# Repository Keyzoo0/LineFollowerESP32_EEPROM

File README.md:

<div align="center">

# 🤖 Robot Line Follower ESP32 — EEPROM Polinema

**Line follower kompetitif berbasis ESP32 dengan _path-programming on-device_, UI OLED non-blocking, dan 7 profil PID.**
Program lintasan langsung di robot — tanpa laptop, tanpa recompile.

</div>

---

> **🔧 Status:** firmware ini telah di-**refactor total** dari arsitektur _blocking_ menjadi **non-blocking
> (cooperative state machine)** dan dimigrasikan agar **compile bersih di Arduino-ESP32 core v3.x**.
> Diverifikasi dengan `arduino-cli compile` (0 error, 0 warning).

## ✨ Sorotan Fitur

- 🧠 **Path Programming (Plan → Index → Checkpoint)** — sampai **9 plan × 100 langkah**, tiap langkah punya 14 parameter (trigger sensor, aksi, kecepatan 2-fase, PID per-segmen, timer jarak-encoder).
- 🎛️ **UI OLED non-blocking** — navigasi tab/menu responsif, tanpa _freeze_, tanpa konflik antar-menu.
- 📏 **14 sensor IR** via 2× MUX, kalibrasi **auto & manual** + pengaturan sensitivitas.
- 🎚️ **7 profil PID** yang bisa di-tune & dites _live_ di robot.
- 🏁 **Checkpoint resume** + stopwatch waktu tempuh.
- ⚫⚪ **Garis hitam & putih** didukung dalam satu lookup-table, 3 mode follow (center/kanan/kiri).
- 🔋 **Proteksi baterai** (cutoff sebelum start) + indikator persen.
- 🧰 **Tools on-device**: Test Motor, Copy/Mirror Plan, Reset Plan, Set Default, Set Throttle.

---

## 📑 Daftar Isi
1. [Quick Start](#-quick-start)
2. [Hardware](#-hardware)
3. [Arsitektur Non-Blocking](#-arsitektur-non-blocking)
4. [Peta Menu](#-peta-menu)
5. [Path Programming](#-path-programming-planindexcheckpoint)
6. [Profil PID](#-profil-pid)
7. [Apa yang Berubah di Refactor Ini](#-apa-yang-berubah-di-refactor-ini)
8. [Peta Memori](#-peta-memori)
9. [Struktur Proyek](#-struktur-proyek)
10. [Roadmap](#-roadmap)
11. [Kredit & Lisensi](#-kredit--lisensi)

---

## 🚀 Quick Start

<details open>
<summary><b>Build via arduino-cli (cara yang dipakai untuk verifikasi)</b></summary>

```bash
# 1. Pasang core ESP32 v3.x
arduino-cli config add board_manager.additional_urls https://espressif.github.io/arduino-esp32/package_esp32_index.json
arduino-cli core update-index
arduino-cli core install esp32:esp32

# 2. Pasang library
arduino-cli lib install "Adafruit GFX Library" "Adafruit SH110X" "Adafruit PCF8574" "SPIMemory"

# 3. Compile
arduino-cli compile --fqbn esp32:esp32:esp32 LineFollowerESP32_EEPROM

# 4. Upload (ganti /dev/ttyUSB0 sesuai port)
arduino-cli upload  --fqbn esp32:esp32:esp32 -p /dev/ttyUSB0 LineFollowerESP32_EEPROM
```
</details>

<details>
<summary><b>Build via Arduino IDE</b></summary>

1. **Boards Manager** → pasang `esp32 by Espressif` (versi 3.x).
2. **Library Manager** → pasang: Adafruit GFX, Adafruit SH110X, Adafruit PCF8574, SPIMemory.
3. Buka folder `LineFollowerESP32_EEPROM/`, pilih board **ESP32 Dev Module**, lalu Upload.
</details>

> ⚠️ **Setelah flash pertama**, jalankan menu **Settings → Set Default** sekali untuk menginisialisasi
> layout memori baru (`VAL_INDEX` kini 100). Lalu **Calib Sensor → Auto** untuk kalibrasi lintasan.

---

## 🔩 Hardware

| Subsistem | Komponen | Pin / Alamat |
|-----------|----------|--------------|
| **MCU** | ESP32 (240 MHz) | — |
| **Sensor garis** | 14× IR analog via 2× MUX 8-kanal (7 kiri + 7 kanan) | ADC `32` (kiri), `35` (kanan); selektor `13/14/15` |
| **Driver motor** | H-bridge (BTS7960), PWM LEDC 15 kHz / 8-bit | Kiri `26/27` · Kanan `17/16` |
| **Encoder** | 2× rotary quadrature (CPR 208, roda Ø17 mm) | Kiri `33/25` · Kanan `39/36` |
| **Display** | OLED SH1106 128×64 I²C | `0x3C` |
| **Tombol** | 6 tombol via PCF8574 (I²C expander) | `0x27` |
| **Memori lintasan** | SPI Flash Winbond 4MB (SPIMemory) | CS `5` |
| **Memori konfigurasi** | EEPROM emulasi 1 KB | — |
| **Baterai** | ADC + divider 10k/3.3k, filter EMA, cutoff 11.8 V | `34` |
| **LED status** | indikator tulis memori | `12` |

> PCB (KiCad) & model 3D tersedia di folder [`Electrical/`](Electrical) dan [`3d Model/`](3d%20Model).

---

## 🧩 Arsitektur Non-Blocking

Versi lama menjebak eksekusi di `while(1)` tiap menu (blocking) + tombol _busy-wait_ + state global dipakai
bersama → tidak responsif & sering konflik antar-menu. Versi ini memakai **loop kooperatif**:

```mermaid
flowchart LR
    L([loop]) --> I[inputUpdate<br/>baca 6 tombol sekali<br/>edge + auto-repeat]
    I --> H[uiHandle<br/>logika layar aktif]
    H --> F{sudah 33 ms?}
    F -- ya --> R[uiRender<br/>1x lcd.display per frame]
    F -- tidak --> L
    R --> L
```

**3 pilar yang menghilangkan blocking & konflik:**

| Pilar | Sebelum | Sesudah |
|-------|---------|---------|
| **Input** | `touchUp()` _busy-wait_ menunggu tombol dilepas | `inputUpdate()` non-blocking → event `PRESS / HOLD / RELEASE` (debounce + auto-repeat berbasis `millis()`) |
| **Render** | `clearDisplay()/display()` berserak di tiap layar | satu `lcd.display()` per frame (~30 fps) |
| **State** | global `selectSet/countMenu/halIdx` dipakai bersama | tiap layar punya **struct state lokal** + **screen stack** (push/pop) |

Navigasi antar-layar memakai state machine + stack:

```mermaid
stateDiagram-v2
    [*] --> HOME
    HOME --> MENU: OK
    HOME --> SETINDEX: Set Plan
    HOME --> CHECKPOINT
    HOME --> CALIB
    HOME --> RACE: RUN (mode C)
    HOME --> TUNEPID: RUN (mode F)
    MENU --> SETTINGS
    MENU --> TUNEPID
    MENU --> TESTMOTOR
    MENU --> COPYMIRROR
    MENU --> RESETPLAN
    SETINDEX --> ADDREMOVE
    SETTINGS --> SETDEFAULT
    SETTINGS --> THROTTLE
    RACE --> RACE_RESULT
    RACE_RESULT --> HOME
```

> 🏁 **Mode balapan** sengaja tetap _tight loop_ real-time (deterministik untuk kontrol), namun tombol
> abort dibaca non-blocking dan **semua timing pakai `millis()`** (tanpa `delay()`), jadi abort tetap responsif.

---

## 🗺️ Peta Menu

<details open>
<summary><b>Pohon menu lengkap</b></summary>

```
HOME ── UP/DOWN pindah widget · RUN = mulai ──────────────────────────
├─ Mode C/F        C=Balapan, F=Tune PID   ·  OK → MAIN MENU
├─ Set Plan        pilih plan (1–9)         ·  OK → SET INDEX
├─ Normal Speed    ±5
├─ CHKPNT          OK → CHECKPOINT
└─ CALSEN          OK → CALIB SENSOR

MAIN MENU ── UP/DOWN · RUN = back ────────────────────────────────────
├─ Set Plan          OK → SET INDEX
├─ Calib Sensor      +:Auto   -:Manual
├─ Tuning PID        OK → TUNE PID
├─ Test Motor        OK → TEST MOTOR
├─ Copy Mirror Plan  OK → COPY/MIRROR
├─ Delete Plan       OK → RESET PLAN
└─ Settings          OK → SETTINGS (Set Default · Set Throttle)

SET INDEX ── editor langkah (list datar, 15 baris) ───────────────────
   Index · Trig SLog · Trig Logic · Action · Speed L/R · Act Delay ·
   PID Prof · Speed A · Timer A · Mode TIM · Speed B · Timer B ·
   UsedSens · FL Mode      (OK di baris "Index" → ADD/REMOVE langkah)
```
</details>

**Tombol:** `OK` pilih/masuk · `UP/DOWN` navigasi · `+ / -` ubah nilai (tahan = auto-repeat) · `RUN` kembali/mulai.

---

## 🧠 Path Programming (Plan/Index/Checkpoint)

Robot menjalankan **program lintasan** yang tersimpan, bukan sekadar mengikuti garis.

- **Plan** = satu lintasan penuh (ada **9** plan).
- **Index** = satu langkah dalam plan (ada **100** langkah/plan). Tiap langkah menyimpan:

| Parameter | Fungsi |
|-----------|--------|
| `Trig SLog` + `Trig Logic` | **Pemicu**: pola sensor + logika `OR / AND / TIM / XOR` |
| `Action` | aksi saat terpicu: `STOP/FORWARD/LEFT/RIGHT/BACKWARD/PICK/DROP/TLEFT/TRIGHT/FAN` |
| `Speed L/R` + `Act Delay` | kecepatan & durasi aksi |
| `Speed A/B` + `Timer A/B` | **2 fase kecepatan** dengan ramp berbeda |
| `Mode TIM` | sumber timer: waktu `mS` atau **jarak encoder** `CmR/CmL` |
| `PID Prof` | profil PID per-segmen (Normal..Profil 6) |
| `UsedSens` | masking sensor pinggir (All / Ignore 1–3 sisi) |
| `FL Mode` | sisi garis: `FLC` center · `FLR` kanan · `FLL` kiri |

- **Checkpoint** = titik _resume_; robot bisa lanjut balapan dari langkah tertentu (8 CP/plan).

```mermaid
flowchart TD
    S[start] --> RD[baca sensor]
    RD --> TR{pemicu langkah<br/>terpenuhi?}
    TR -- tidak --> PID[ikuti garis PID<br/>normalSpeed] --> RD
    TR -- ya --> ACT[eksekusi Action] --> A[fase A: ramp ke Speed A<br/>selama Timer A]
    A --> B[fase B: ramp ke Speed B<br/>selama Timer B]
    B --> ST{langkah == stop?}
    ST -- tidak --> NX[langkah++] --> RD
    ST -- ya --> F([selesai: tampil waktu])
```

---

## 🎚️ Profil PID

7 profil tersimpan di EEPROM, di-tune lewat **Tuning PID** (+ uji _live_ "Coba PID"):

| Profil | Kp | Ki | Kd | Target v |
|:------:|:--:|:--:|:--:|:--------:|
| Normal | 3.0 | 0.00 | 10 | 50 |
| Profil 1 | 7.0 | 0.02 | 12 | 80 |
| Profil 2 | 7.0 | 0.02 | 15 | 100 |
| Profil 3 | 7.4 | 0.04 | 35 | 120 |
| Profil 4 | 7.4 | 0.04 | 40 | 140 |
| Profil 5 | 7.4 | 0.04 | 50 | 160 |
| Profil 6 | 7.4 | 0.04 | 60 | 180 |

Hukum kontrol: `move = error·Kp + ΣError·Ki + Δerror·Kd` → `kiri = v − move`, `kanan = v + move` (clamp ±255).

---

## 🔄 Apa yang Berubah di Refactor Ini

<details>
<summary><b>🐞 Bug yang diperbaiki</b></summary>

| # | Bug | Perbaikan |
|---|-----|-----------|
| 1 | `VAL_INDEX=50` tapi UI memakai index 0–99 → **buffer overflow** | dinaikkan ke **100** + serialisasi flash diperbarui |
| 2 | Hanya 5 dari 9 plan dibaca saat boot (`readIdx` loop `<5`) | dimuat penuh `< VAL_PLAN` |
| 3 | `analogReadResolution(8)` vs kalibrasi skala 1023 | disamakan ke **10-bit** (battery ikut diperbaiki ÷1023) |
| 4 | `accelTA/accelTB` diatur tapi tak dipakai | kini **benar-benar dipakai** sebagai step ramp fase A/B |
| 5 | Transfer Plan tak terjangkau / stub | dihapus dari menu (out-of-scope) |
| 6 | `guiTestMotor` `speedsR == 255` (operator salah) | ditulis ulang dengan clamp benar |
| 7 | Duplikasi `struct Plan/CP` global (~15 KB) + bug sinkronisasi | dihapus, serialisasi via blob transien |

</details>

<details>
<summary><b>⚙️ Migrasi Arduino-ESP32 v3.x (LEDC)</b></summary>

| Lama (v2.x) | Baru (v3.x) |
|-------------|-------------|
| `ledcSetup(ch, freq, res)` + `ledcAttachPin(pin, ch)` | `ledcAttach(pin, freq, res)` |
| `ledcWrite(ch, duty)` | `ledcWrite(pin, duty)` |

Terisolasi di `motor.ino` — logika kontrol tidak berubah.
</details>

---

## 💾 Peta Memori

**EEPROM (1 KB)** — konfigurasi: home (0–3), sensitivity (4), max/min sensor (6–61), kalibrasi (62–89),
Kp/Ki/Kd (90–110), accel (111–112).

**SPI Flash 4MB** — lintasan: 9 plan × 1700 B + 9 checkpoint × 32 B ≈ **15.6 KB** (muat dalam `eraseBlock32K`).
Serialisasi memakai **blob transien** — tidak ada duplikasi RAM.

---

## 📂 Struktur Proyek

| Lapisan | File | Peran |
|---------|------|-------|
| **Entry** | `LineFollowerESP32_EEPROM.ino` | `setup()` + `loop()` (input → handle → render) |
| **Data** | `data.h`, `storage.ino` | konfigurasi, plan, checkpoint, save/load |
| **Input** | `input.h`, `input.ino` | tombol non-blocking (PCF8574) |
| **UI** | `ui.h`, `ui.ino` | state machine + dispatcher |
| **Layar** | `screens_main.ino`, `screens_index.ino`, `screens_tools.ino` | semua menu |
| **Kontrol** | `PID.ino`, `sensor.ino`, `motor.ino`, `encoder.ino`, `race.ino` | follow line + balapan |
| **Display** | `oled.h`, `oled.ino` | SH1106 + bitmap + helper gambar |
| **Util** | `timer.h` | stopwatch millis |

---

## 🛣️ Roadmap

Fitur berikut sengaja **di-tunda** (hardware belum ada / out-of-scope) agar fokus pada line follower:

- [ ] Transfer Plan (robot ↔ robot)
- [ ] Gripper & Fan (aksi `PICK/DROP/FAN` kini no-op)
- [ ] Setting Encoder (PID kecepatan)
- [ ] Wi-Fi + OTA Update
- [ ] Mode Transporter

---

## 🙏 Kredit & Lisensi

Dirancang oleh **Komunitas EEPROM Polinema** (tim G14/G15).
Refactor arsitektur non-blocking & migrasi core v3.x.

Lisensi **MIT** © 2024 [Keyzoo0](https://github.com/Keyzoo0) — lihat [LICENSE](LICENSE).

<div align="center">

⭐ _Kalau proyek ini membantu, kasih bintang ya!_ ⭐

</div>

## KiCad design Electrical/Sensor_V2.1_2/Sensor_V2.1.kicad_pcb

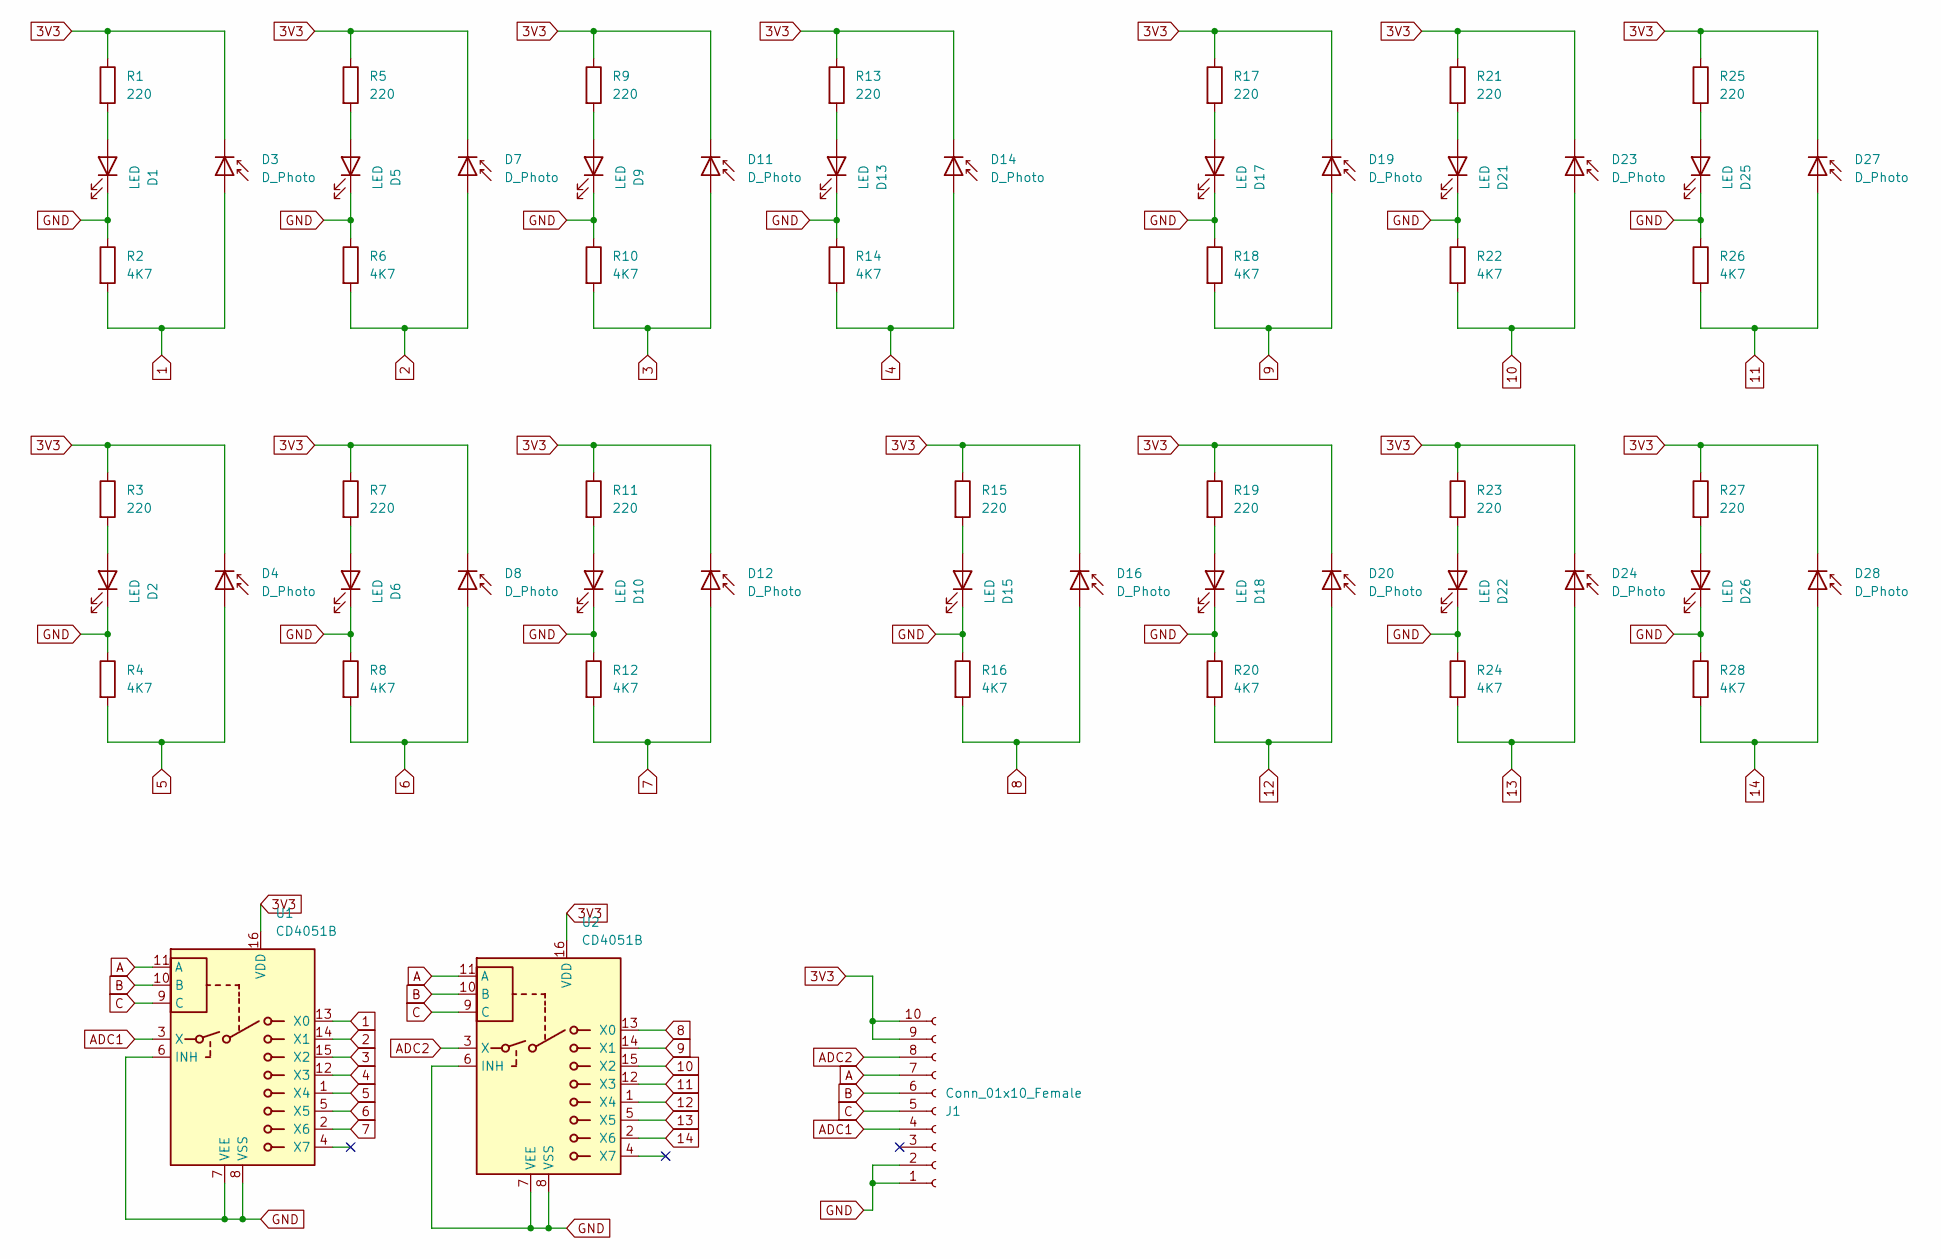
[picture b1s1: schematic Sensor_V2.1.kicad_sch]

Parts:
D1, D2, D5, D6, D9, D10, D13, D15, D17, D18, D21, D22, D25, D26: LED; LED_D3.0mm
D3, D4, D7, D8, D11, D12, D14, D16, D19, D20, D23, D24, D27, D28: D_Photo; LED_D3.0mm
J1: Conn_01x10_Female; TE_1-84952-0_1x10-1MP_P1.0mm_Horizontal
R1, R3, R5, R7, R9, R11, R13, R15, R17, R19, R21, R23, R25, R27: 220; R_0805_2012Metric_Pad1.20x1.40mm_HandSolder
R2, R4, R6, R8, R10, R12, R14, R16, R18, R20, R22, R24, R26, R28: 4K7; R_0805_2012Metric_Pad1.20x1.40mm_HandSolder
U1, U2: CD4051B; SOIC-16_3.9x9.9mm_P1.27mm

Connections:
1: D3.2 (A), R2.2, U1.13 (X0)
2: D7.2 (A), R6.2, U1.14 (X1)
3: D11.2 (A), R10.2, U1.15 (X2)
3V3: D3.1 (K), D4.1 (K), D7.1 (K), D8.1 (K), D11.1 (K), D12.1 (K), D14.1 (K), D16.1 (K), D19.1 (K), D20.1 (K), D23.1 (K), D24.1 (K), D27.1 (K), D28.1 (K), J1.9, J1.10, R1.1, R3.1, R5.1, R7.1, R9.1, R11.1, R13.1, R15.1, R17.1, R19.1, R21.1, R23.1, R25.1, R27.1, U1.16 (VDD), U2.16 (VDD)
4: D14.2 (A), R14.2, U1.12 (X3)
5: D4.2 (A), R4.2, U1.1 (X4)
6: D8.2 (A), R8.2, U1.5 (X5)
7: D12.2 (A), R12.2, U1.2 (X6)
8: D16.2 (A), R16.2, U2.13 (X0)
9: D19.2 (A), R18.2, U2.14 (X1)
10: D23.2 (A), R22.2, U2.15 (X2)
11: D27.2 (A), R26.2, U2.12 (X3)
12: D20.2 (A), R20.2, U2.1 (X4)
13: D24.2 (A), R24.2, U2.5 (X5)
14: D28.2 (A), R28.2, U2.2 (X6)
A: J1.7, U1.11 (A), U2.11 (A)
ADC1: J1.4, U1.3 (X)
ADC2: J1.8, U2.3 (X)
B: J1.6, U1.10 (B), U2.10 (B)
C: J1.5, U1.9 (C), U2.9 (C)
GND: D1.1 (K), D2.1 (K), D5.1 (K), D6.1 (K), D9.1 (K), D10.1 (K), D13.1 (K), D15.1 (K), D17.1 (K), D18.1 (K), D21.1 (K), D22.1 (K), D25.1 (K), D26.1 (K), J1.1, J1.2, R2.1, R4.1, R6.1, R8.1, R10.1, R12.1, R14.1, R16.1, R18.1, R20.1, R22.1, R24.1, R26.1, R28.1, U1.6 (INH), U1.7 (VEE), U1.8 (VSS), U2.6 (INH), U2.7 (VEE), U2.8 (VSS)
unnamed: D1.2 (A), R1.2
unnamed: D2.2 (A), R3.2
unnamed: D5.2 (A), R5.2
unnamed: D6.2 (A), R7.2
unnamed: D9.2 (A), R9.2
unnamed: D10.2 (A), R11.2
unnamed: D13.2 (A), R13.2
unnamed: D15.2 (A), R15.2
unnamed: D17.2 (A), R17.2
unnamed: D18.2 (A), R19.2
unnamed: D21.2 (A), R21.2
unnamed: D22.2 (A), R23.2
unnamed: D25.2 (A), R25.2
unnamed: D26.2 (A), R27.2

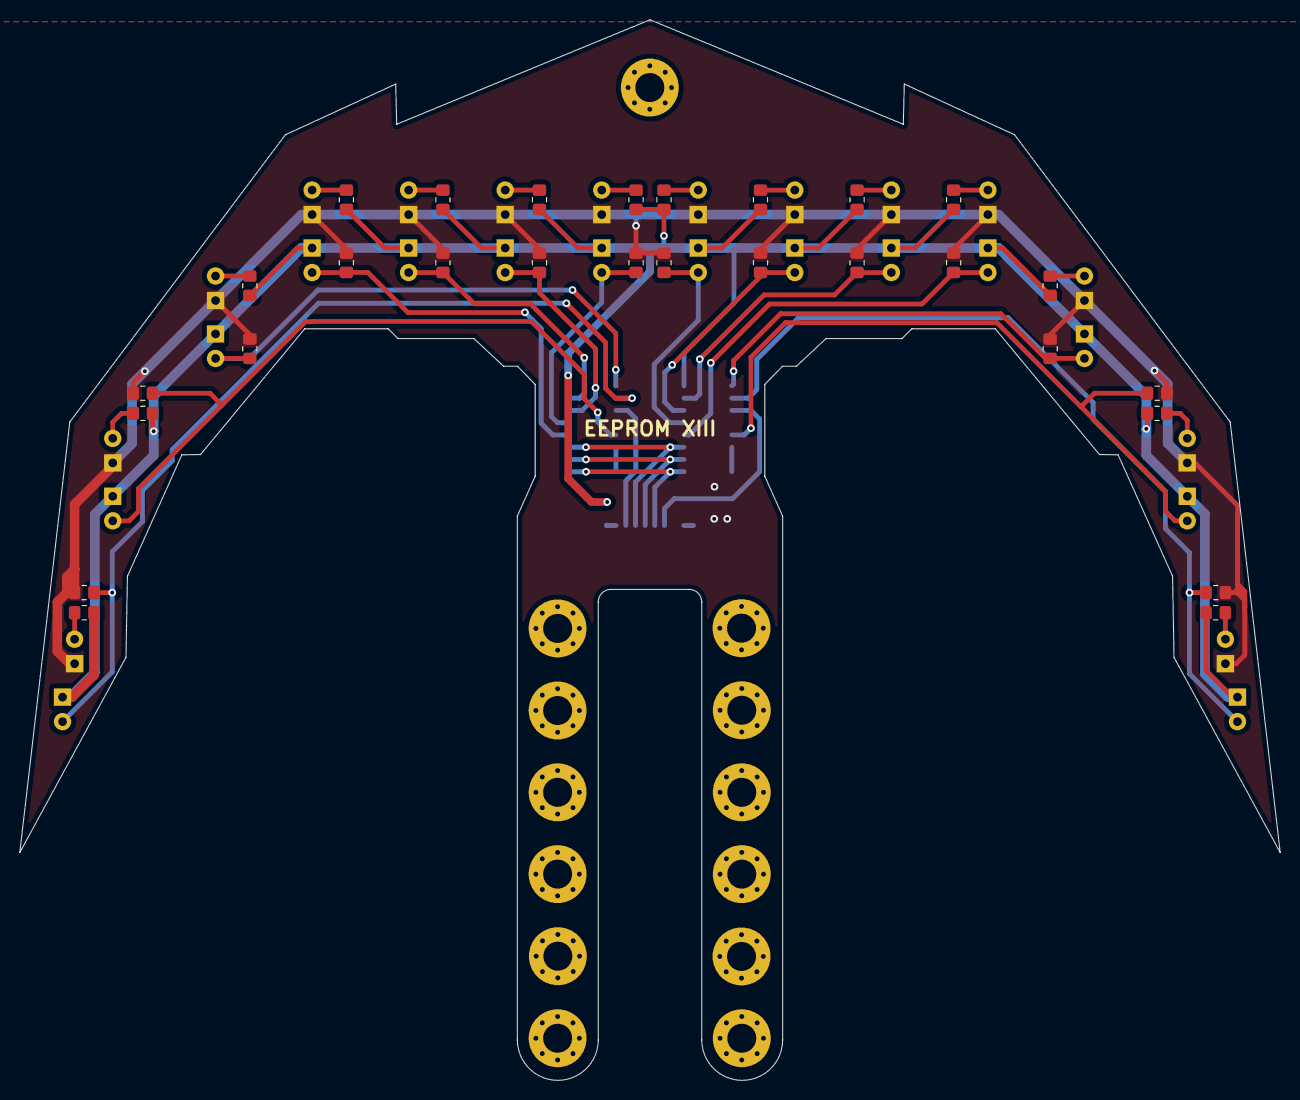
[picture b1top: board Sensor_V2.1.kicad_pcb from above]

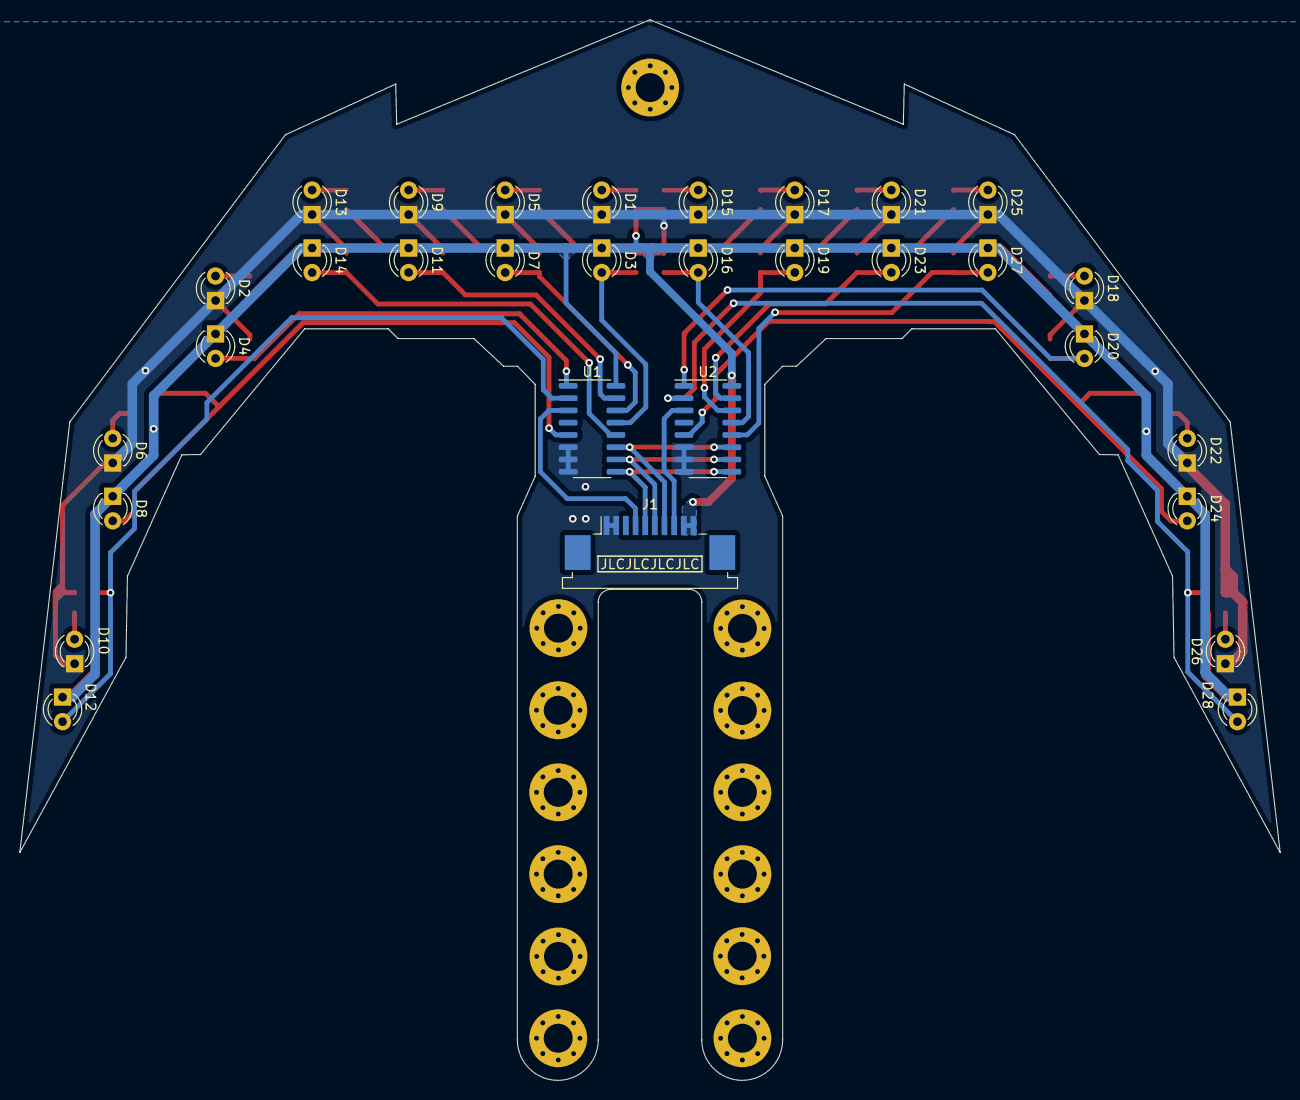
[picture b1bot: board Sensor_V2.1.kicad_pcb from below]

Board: 2 copper layers, 130.6 x 109.9 mm, 72 parts (31 on the bottom side), 35 nets.

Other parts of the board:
H1, H4, H5, H6, H7, H8, H10, H12, H13, H14, H15, H17, H21: MountingHole; MountingHole_3mm_Pad_Via

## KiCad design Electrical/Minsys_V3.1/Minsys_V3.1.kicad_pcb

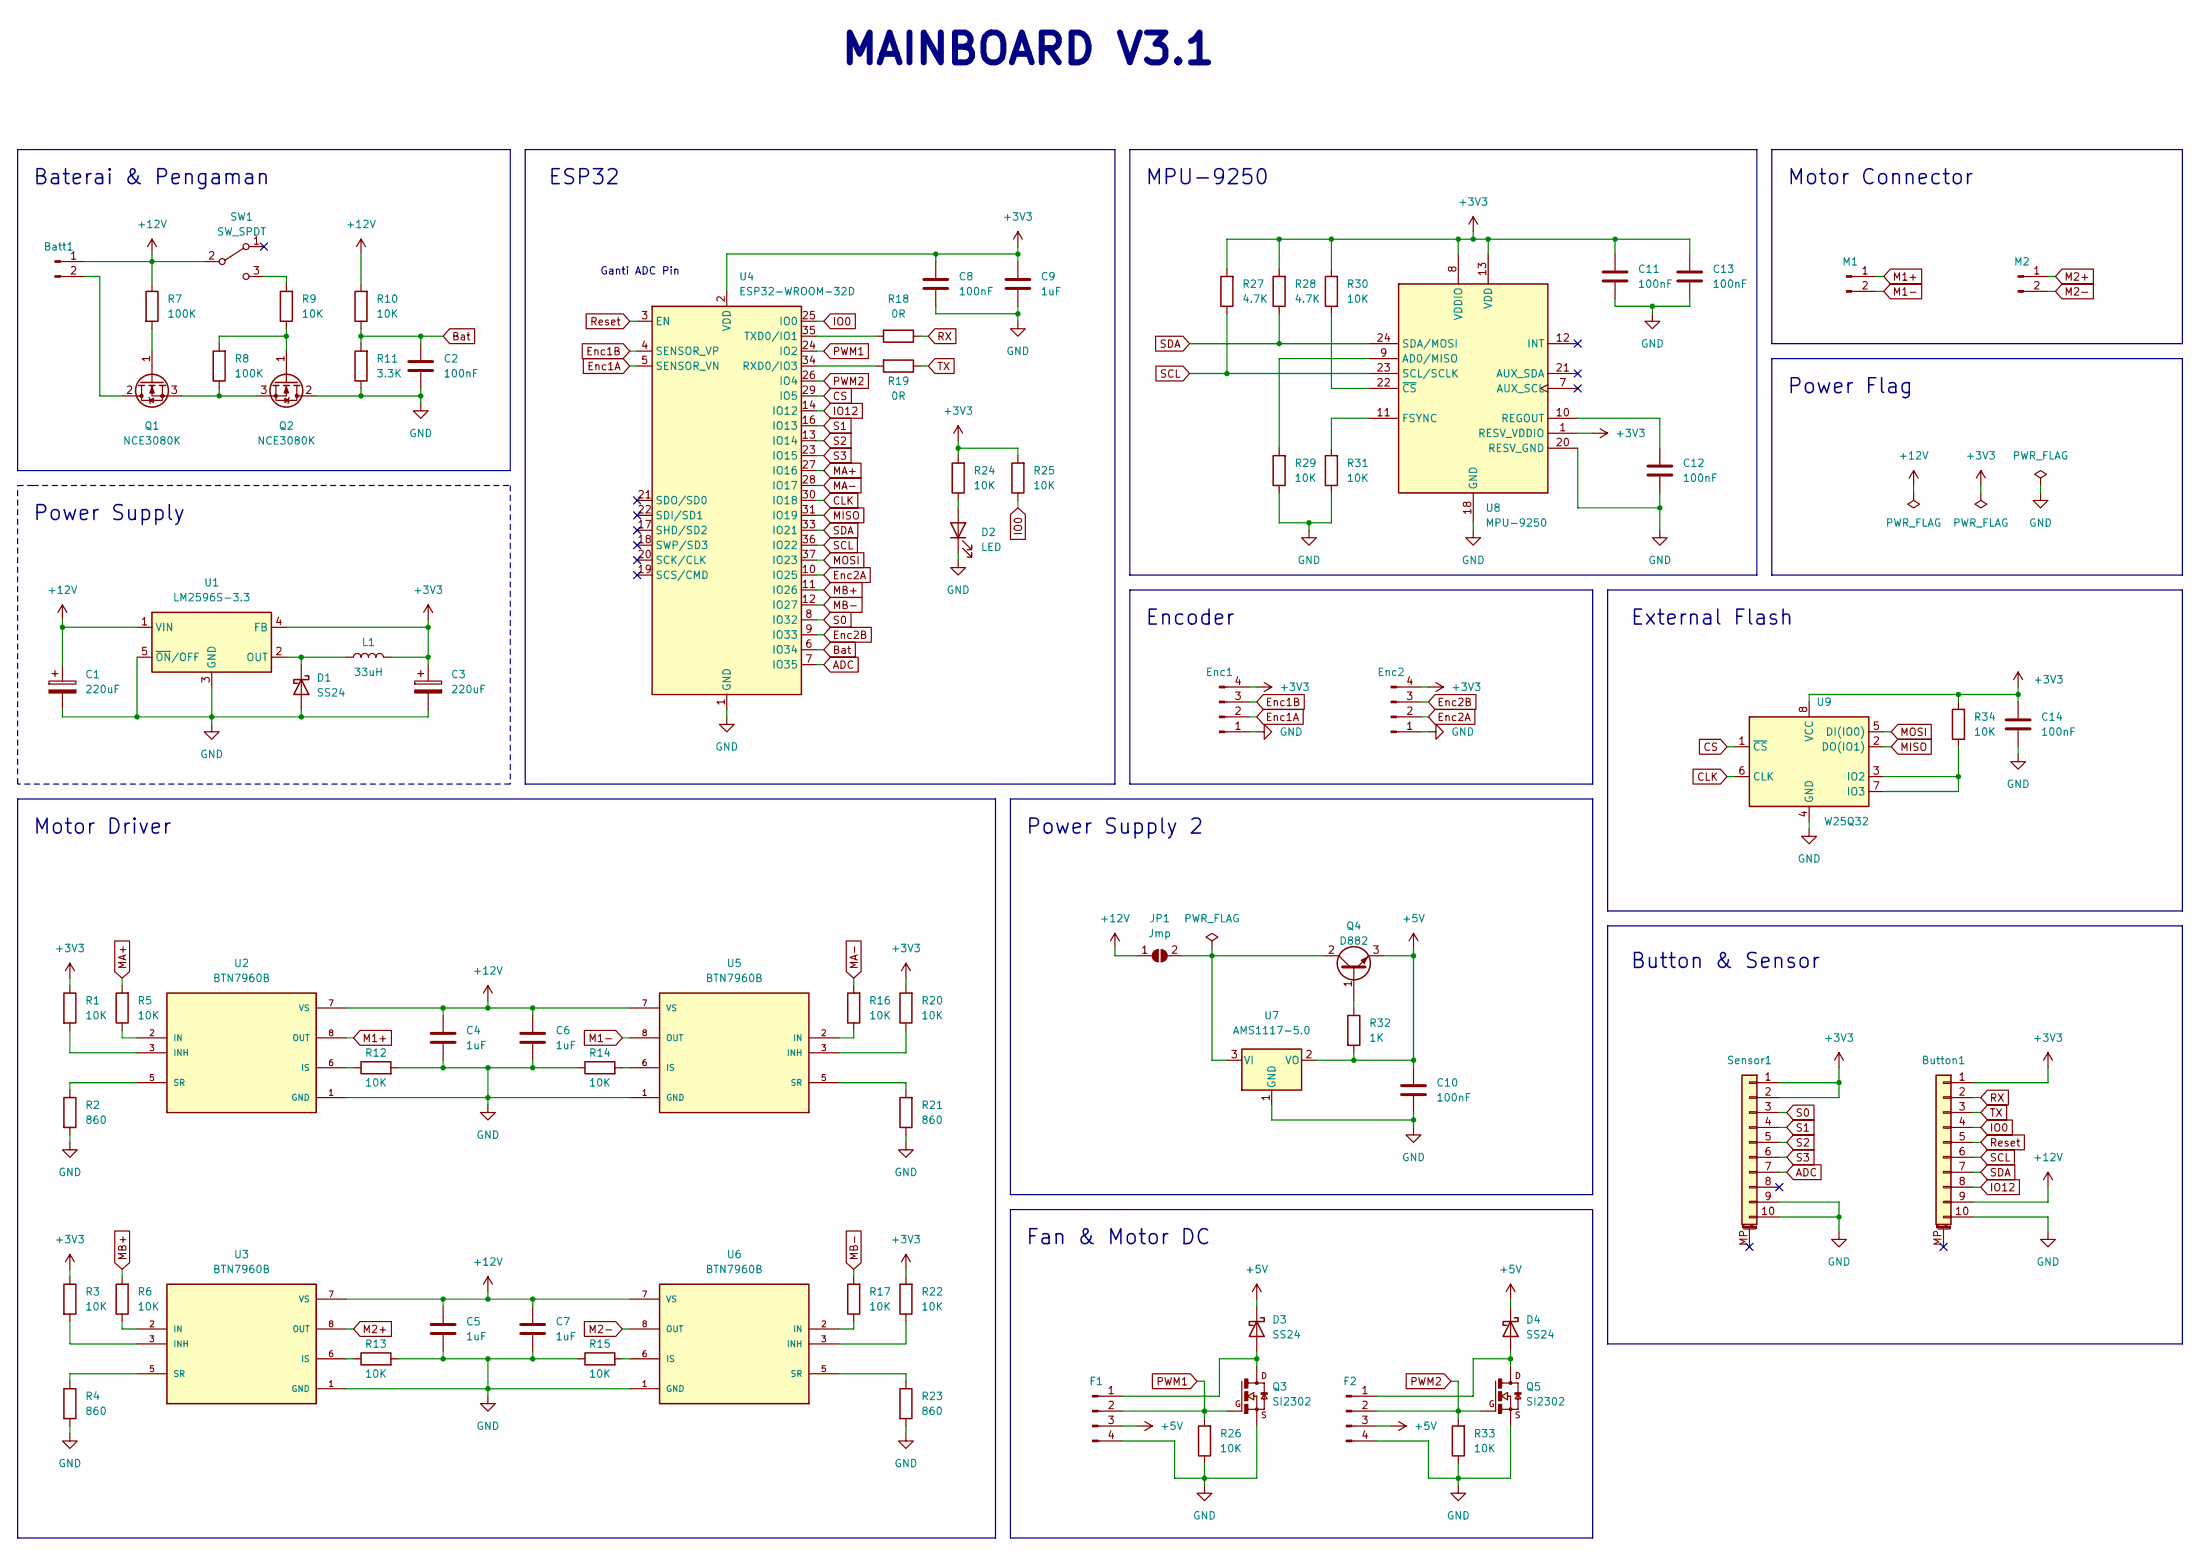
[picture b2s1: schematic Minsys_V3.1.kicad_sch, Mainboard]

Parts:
Batt1: Conn_01x02_Male; PinHeader_1x02_P2.54mm_Vertical
Button1: Conn_01x10_MountingPin; TE_1-84952-0_1x10-1MP_P1.0mm_Horizontal
C1, C3: 220uF; CP_Elec_6.3x5.4
C2, C8, C10, C11, C12, C13, C14: 100nF; C_0805_2012Metric_Pad1.18x1.45mm_HandSolder
C4, C5, C6, C7, C9: 1uF; C_0805_2012Metric_Pad1.18x1.45mm_HandSolder
D1, D3, D4: SS24; DO_214
D2: LED; LED_0805_2012Metric_Pad1.15x1.40mm_HandSolder
Enc1, Enc2: Conn_01x04_Male
F1, F2: Conn_01x04_Male; PinHeader_1x04_P2.54mm_Vertical
JP1: Jmp; SolderJumper-2_P1.3mm_Open_Pad1.0x1.5mm
L1: 33uH; L_12x12mm_H6mm
M1, M2: Motor_Pad; Motor_Connetor
Q1, Q2: NCE3080K; TO-252-2
Q3, Q5: SI2302; SOT-23
Q4: D882; SOT-89-3_Handsoldering
R1, R3, R5, R6, R9, R10, R12, R13, R14, R15, R16, R17, R20, R22, R24, R25, R26, R29, R30, R31, R33, R34: 10K; R_0805_2012Metric_Pad1.20x1.40mm_HandSolder
R2, R4, R21, R23: 860; R_0805_2012Metric_Pad1.20x1.40mm_HandSolder
R7, R8: 100K; R_0805_2012Metric_Pad1.20x1.40mm_HandSolder
R11: 3.3K; R_0805_2012Metric_Pad1.20x1.40mm_HandSolder
R18, R19: 0R; R_0805_2012Metric_Pad1.20x1.40mm_HandSolder
R27, R28: 4.7K; R_0805_2012Metric_Pad1.20x1.40mm_HandSolder
R32: 1K; R_0805_2012Metric_Pad1.20x1.40mm_HandSolder
SW1: SW_SPDT; SPDT_Type_2
Sensor1: Conn_01x10_MountingPin; TE_1-84952-0_1x10-1MP_P1.0mm_Horizontal
U1: LM2596S-3.3; TO-263-5_TabPin3
U2, U3, U5, U6: BTN7960B; Infineon_PG-TO-220-7Lead_TabPin8; PARTREV 1.0
U4: ESP32-WROOM-32D; ESP32-WROOM-32
U7: AMS1117-5.0; SOT-223-3_TabPin2
U8: MPU-9250; InvenSense_QFN-24_3x3mm_P0.4mm
U9: W25Q32; SOIC-8_5.23x5.23mm_P1.27mm; PARTREV F

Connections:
+3V3: Button1.1, C3.1, C8.1, C9.1, C11.1, C13.1, C14.1, Enc1.4, Enc2.4, L1.2, R1.1, R3.1, R20.2, R22.2, R24.2, R25.2, R27.2, R28.2, R30.2, R34.2, Sensor1.1, Sensor1.2, U1.4 (FB), U4.2 (VDD), U8.1 (RESV_VDDIO), U8.8 (VDDIO), U8.13 (VDD), U9.8 (VCC)
+5V: C10.1, D3.1 (K), D4.1 (K), F1.3, F2.3, Q4.3, R32.2, U7.2 (VO)
+12V: Batt1.1, Button1.9, C1.1, C4.1, C5.1, C6.1, C7.1, JP1.1 (A), R7.1, R10.2, SW1.2 (B), U1.1 (VIN), U2.7 (VS), U3.7 (VS), U5.7 (VS), U6.7 (VS)
ADC: Sensor1.7, U4.7 (IO35)
Bat: C2.1, R10.1, R11.2, U4.6 (IO34)
CLK: U4.30 (IO18), U9.6 (CLK)
CS: U4.29 (IO5), U9.1 (~CS)
Enc1A: Enc1.2, U4.5 (SENSOR_VN)
Enc1B: Enc1.3, U4.4 (SENSOR_VP)
Enc2A: Enc2.2, U4.10 (IO25)
Enc2B: Enc2.3, U4.9 (IO33)
GND: Button1.10, C1.2, C2.2, C3.2, C4.2, C5.2, C6.2, C7.2, C8.2, C9.2, C10.2, C11.2, C12.2, C13.2, C14.2, D1.2 (A), D2.1 (K), Enc1.1, Enc2.1, F1.4, F2.4, Q2.2 (D), Q3.2, Q5.2, R2.2, R4.2, R11.1, R12.2, R13.2, R14.1, R15.1, R21.1, R23.2, R26.1, R29.1, R31.1, R33.1, Sensor1.9, Sensor1.10, U1.3 (GND), U1.5 (~ON/OFF), U2.1 (GND), U3.1 (GND), U4.1 (GND), U4.15 (GND), U4.38 (GND), U4.39 (GND), U5.1 (GND), U6.1 (GND), U7.1 (GND), U8.18 (GND), U8.20 (RESV_GND), U9.4 (GND)
IO0: Button1.4, R25.1, U4.25 (IO0)
IO12: Button1.8, U4.14 (IO12)
M1+: M1.1, U2.4 (OUT), U2.8 (OUT)
M1-: M1.2, U5.4 (OUT), U5.8 (OUT)
M2+: M2.1, U3.4 (OUT), U3.8 (OUT)
M2-: M2.2, U6.4 (OUT), U6.8 (OUT)
MA+: R5.2, U4.27 (IO16)
MA-: R16.2, U4.28 (IO17)
MB+: R6.2, U4.11 (IO26)
MB-: R17.2, U4.12 (IO27)
MISO: U4.31 (IO19), U9.2 (DO(IO1))
MOSI: U4.37 (IO23), U9.5 (DI(IO0))
unnamed: Batt1.2, Q1.2 (D)
unnamed: C12.1, U8.10 (REGOUT)
unnamed: D1.1 (K), L1.1, U1.2 (OUT)
unnamed: D2.2 (A), R24.1
unnamed: D3.2 (A), F1.1, Q3.3
unnamed: D4.2 (A), F2.1, Q5.3
unnamed: JP1.2 (B), Q4.2, U7.3 (VI)
unnamed: Q1.1 (G), R7.2
unnamed: Q1.3 (S), Q2.3 (S), R8.1
unnamed: Q2.1 (G), R8.2, R9.1
unnamed: Q4.1, R32.1
unnamed: R1.2, U2.3 (INH)
unnamed: R2.1, U2.5 (SR)
unnamed: R3.2, U3.3 (INH)
unnamed: R4.1, U3.5 (SR)
unnamed: R5.1, U2.2 (IN)
unnamed: R6.1, U3.2 (IN)
unnamed: R9.2, SW1.3 (C)
unnamed: R12.1, U2.6 (IS)
unnamed: R13.1, U3.6 (IS)
unnamed: R14.2, U5.6 (IS)
unnamed: R15.2, U6.6 (IS)
unnamed: R16.1, U5.2 (IN)
unnamed: R17.1, U6.2 (IN)
unnamed: R18.2, U4.35 (TXD0/IO1)
unnamed: R19.2, U4.34 (RXD0/IO3)
unnamed: R20.1, U5.3 (INH)
unnamed: R21.2, U5.5 (SR)
unnamed: R22.1, U6.3 (INH)
unnamed: R23.1, U6.5 (SR)
unnamed: R29.2, U8.9 (AD0/MISO)
unnamed: R30.1, U8.22 (~CS)
unnamed: R31.2, U8.11 (FSYNC)
unnamed: R34.1, U9.3 (IO2), U9.7 (IO3)
PWM1: F1.2, Q3.1, R26.2, U4.24 (IO2)
PWM2: F2.2, Q5.1, R33.2, U4.26 (IO4)
RX: Button1.2, R18.1
Reset: Button1.5, U4.3 (EN)
S0: Sensor1.3, U4.8 (IO32)
S1: Sensor1.4, U4.16 (IO13)
S2: Sensor1.5, U4.13 (IO14)
S3: Sensor1.6, U4.23 (IO15)
SCL: Button1.6, R27.1, U4.36 (IO22), U8.23 (SCL/SCLK)
SDA: Button1.7, R28.1, U4.33 (IO21), U8.24 (SDA/MOSI)
TX: Button1.3, R19.1

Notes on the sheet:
Fan & Motor DC
ESP32
Encoder
Motor Driver
Ganti ADC Pin
Motor Connector
Baterai & Pengaman
Power Supply 2
Power Supply
Power Flag
MAINBOARD V3.1
Button & Sensor
MPU-9250
External Flash

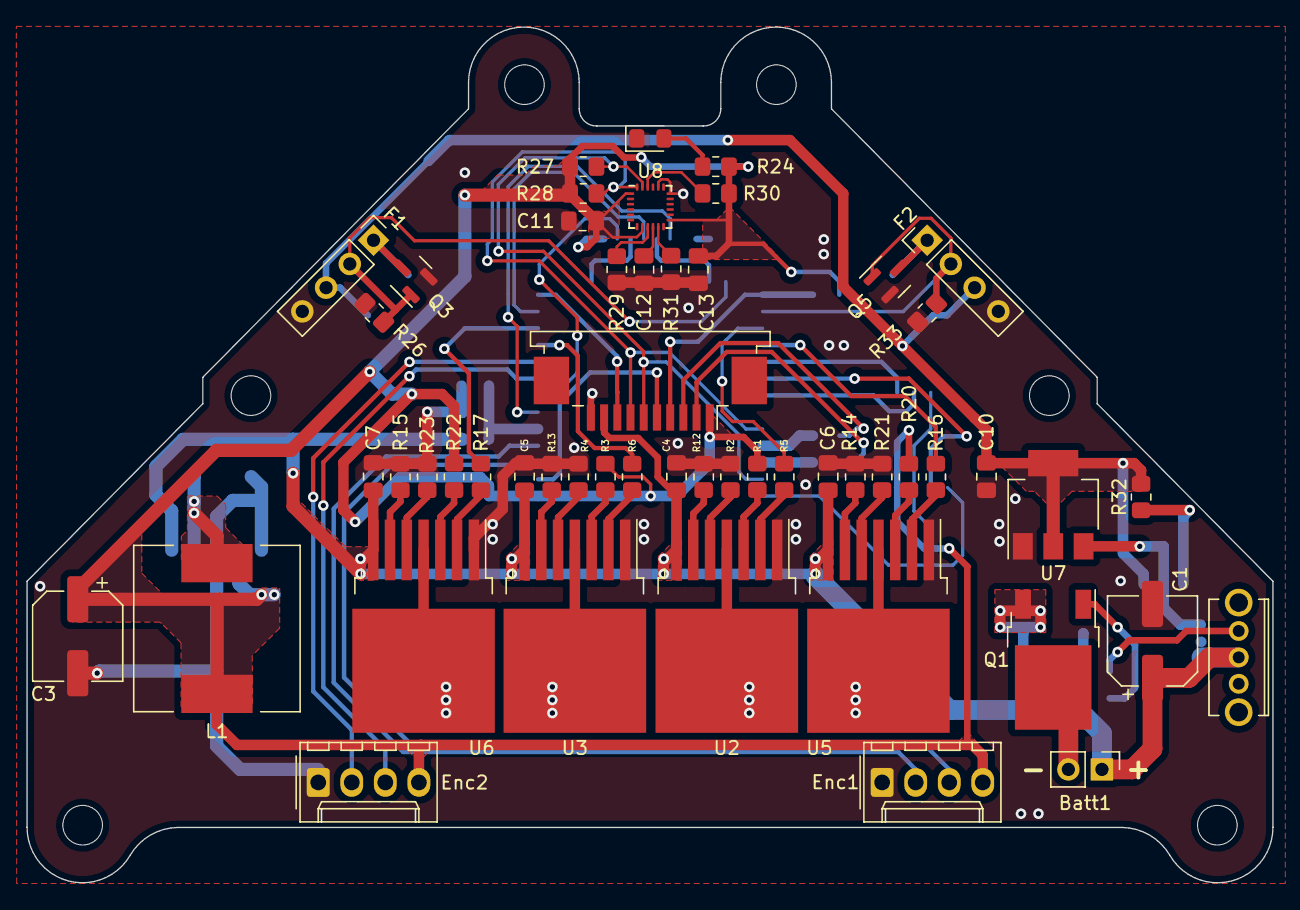
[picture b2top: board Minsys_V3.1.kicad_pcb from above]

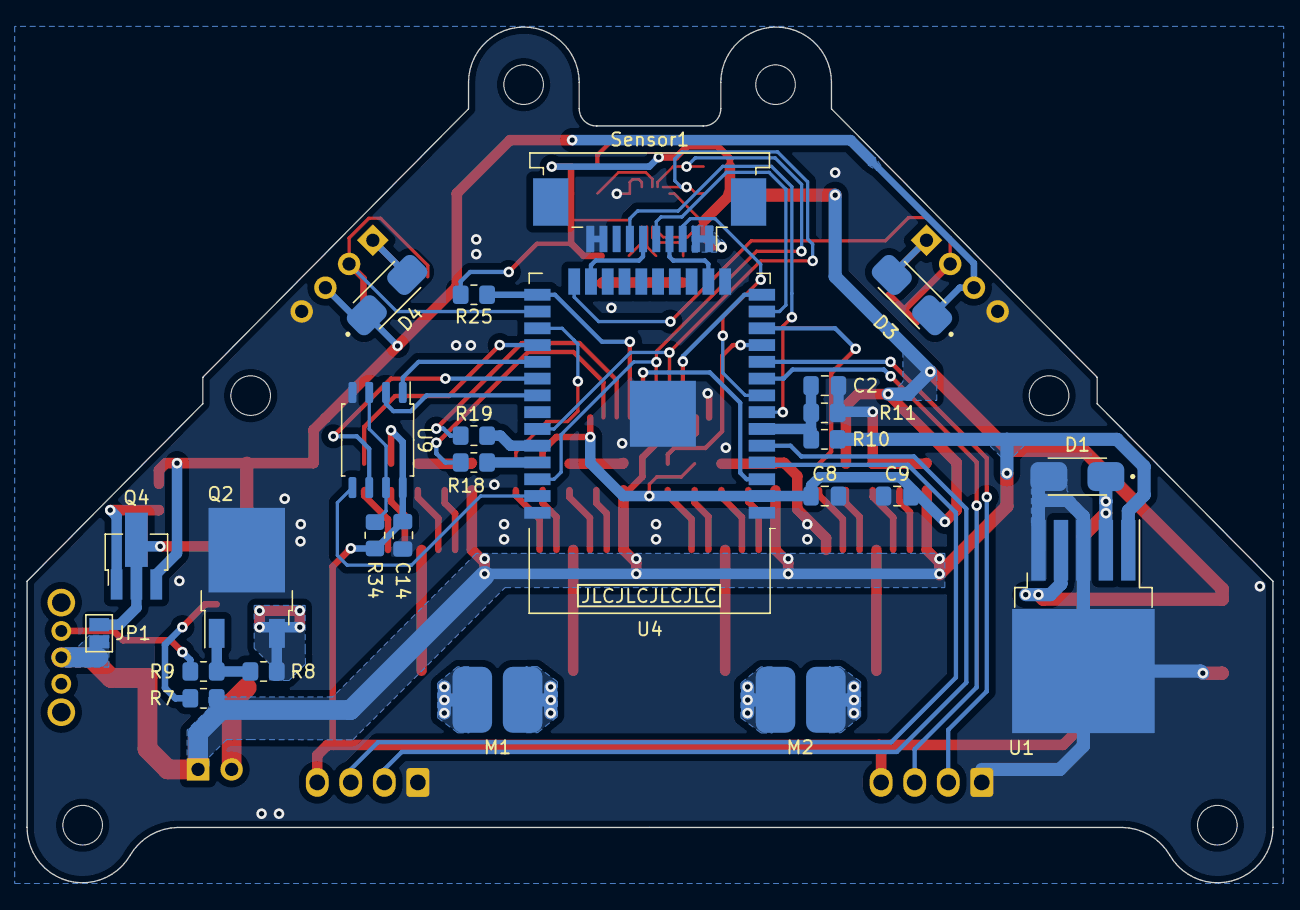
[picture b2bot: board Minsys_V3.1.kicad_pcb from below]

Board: 2 copper layers, 94.3 x 64.8 mm, 84 parts (26 on the bottom side), 69 nets.

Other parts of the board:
H1, H2, H2#2, H2#3, H2#4, H2#5: MountingHole; MountingHole_3mm

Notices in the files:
README.md:
License: MIT
